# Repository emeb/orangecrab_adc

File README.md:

# orangecrab_adc
An ADC and audio FeatherWing to enable SDR experiments with the OrangeCrab

## What is it?
This is an experiment to see if a low-spec SDR system can be easily built
using the OrangeCrab FPGA Feather. It will consist of the ADC / Audio 
"FeatherWing" board which attaches to the OrangeCrab board, along with
gateware to do basic tuning and demodulation. Initial testing will be
static setups, or controlled by USB, but the project may be expanded with
a UI board containing display and buttons / encoders.

## Features
The board comprises the following components:

* AD9203 10-bit / 40MSPS parallel ADC
* 40MHz crystal oscillator
* Analog supply regulation
* 50-ohm SMA input with transformer-coupling to the converter
* TPA6139 Headphone amplifier and 3.5mm jack
* 4-pin I2C bus extension (power, clock, data, gnd)

## Schematic

## Status
* 2020-07-24: The preliminary board design is complete and boards have been
ordered from OSHPark. Parts have been ordered so initial testing should occurr
sometime in early August 2020.

* 2020-08-08: Boards are back from OSHpark and the preliminary test gateware
is working for simple AM broadcast reception. Audio output sounds great -
very clean and clear. 

* 2020-08-09: Corrected missing mount holes in PCB. Updated OSHpark link

https://oshpark.com/shared_projects/GzvQCkin

* 2020-08-18: Added Litex-based controller project

https://github.com/emeb/OrangeCrab-Litex-ADC

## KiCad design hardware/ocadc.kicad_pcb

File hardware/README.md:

# orangecrab_adc - hardware
Hardware design for the orangecrab_adc

This is just the KiCad design. The libraries are probably hosed (as usual)
because your setup isn't the same as mine. Hopefully the rescue libs and
cache have enough that you can see things.

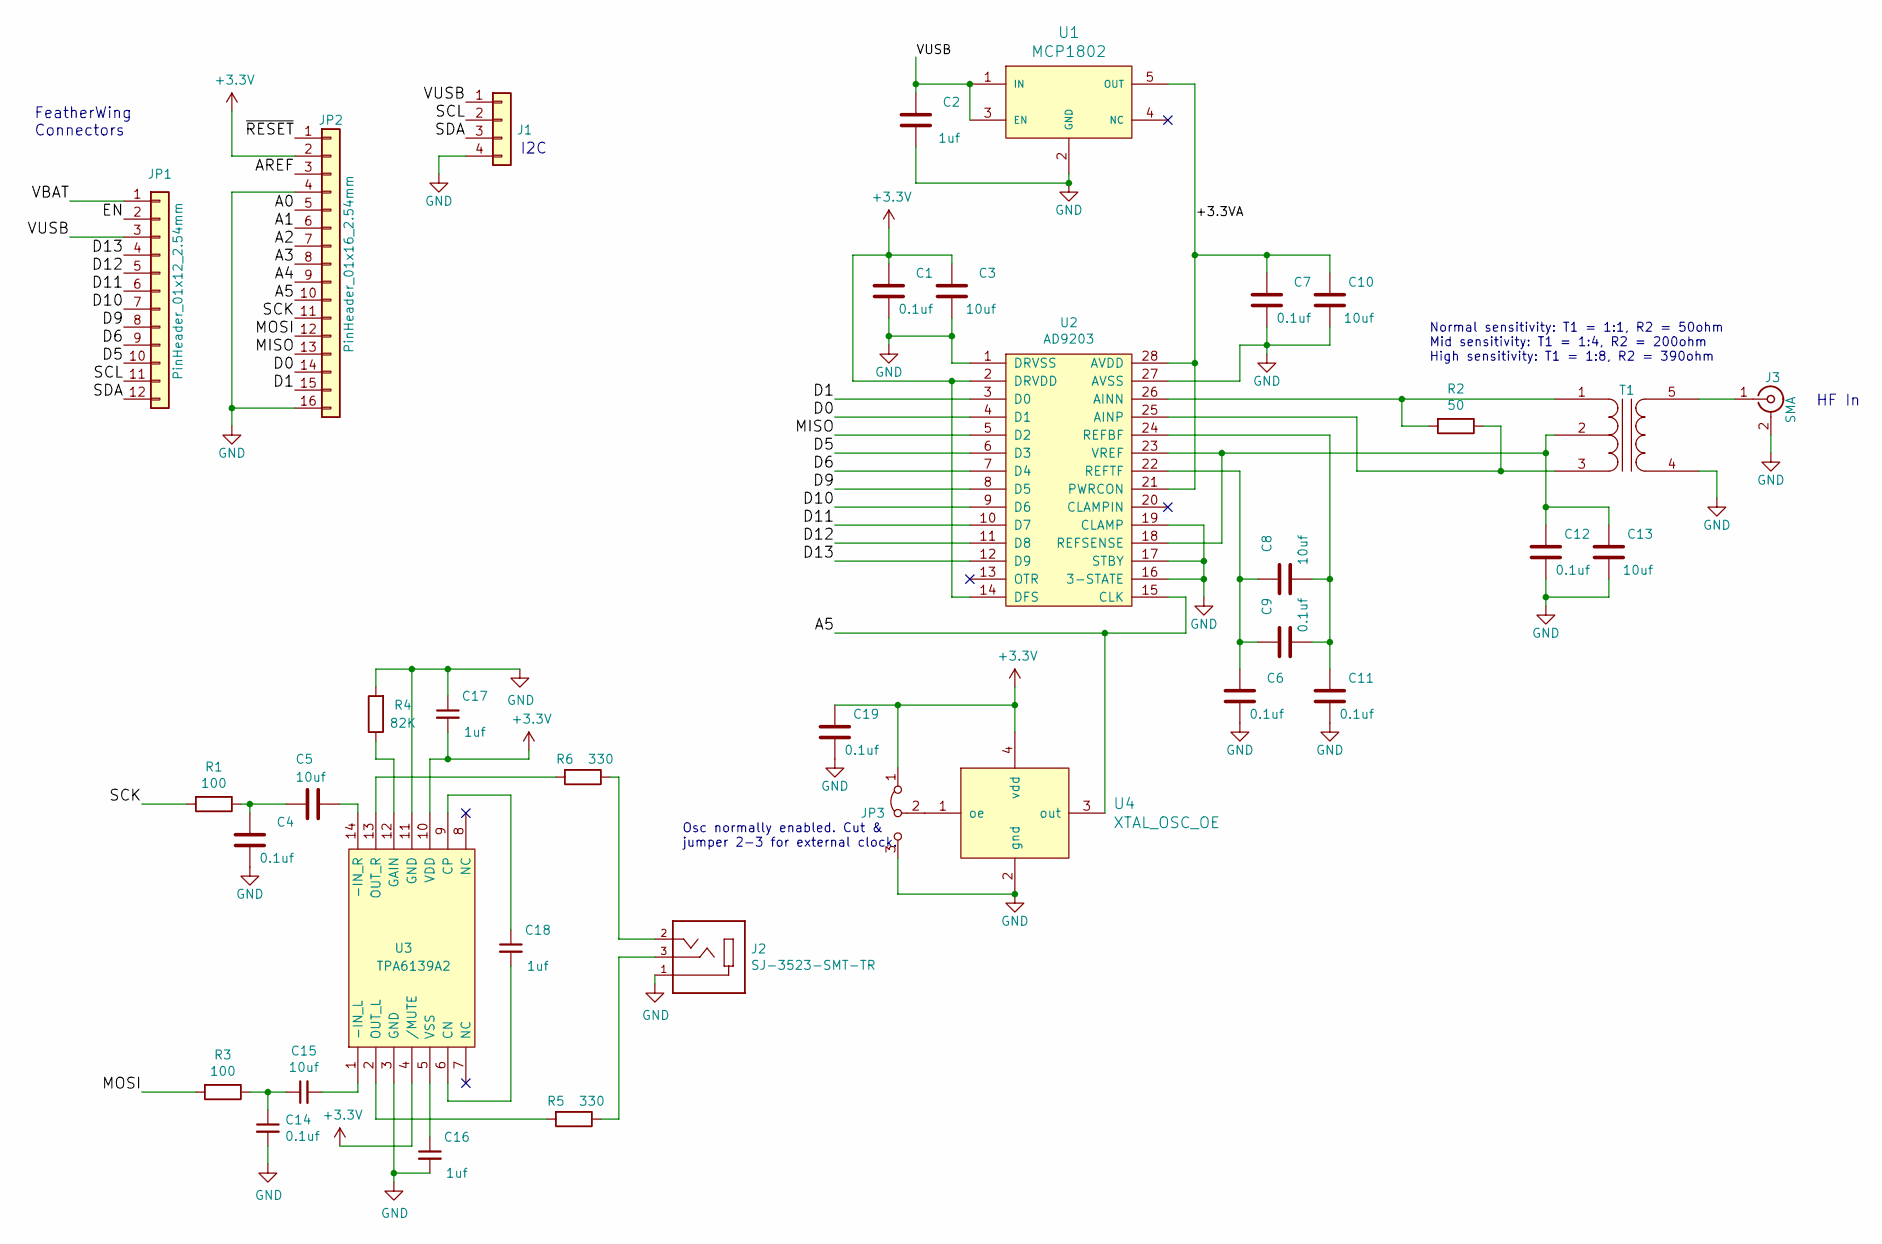
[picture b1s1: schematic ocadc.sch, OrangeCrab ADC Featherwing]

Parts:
C1, C4, C6, C7, C9, C11, C12, C14, C19: 0.1uf; C_0603_HandSoldering
C2, C16, C17, C18: 1uf; C_0603_HandSoldering
C3, C5, C8, C10, C13, C15: 10uf; C_0805_HandSoldering
J1: Conn_01x04; Pin_Header_Straight_1x04_Pitch2.54mm
J2: SJ-3523-SMT-TR; CUI_SJ-3523-SMT-TR
J3: SMA; SMA_END
JP1: PinHeader_01x12_2.54mm; Conn_PinHeader_1x12
JP2: PinHeader_01x16_2.54mm; Conn_PinHeader_1x16
JP3: Jumper_3_Bridged12; SolderJumper-3_P1.3mm_Bridged12_Pad1.0x1.5mm
R1, R3: 100; R_0603_HandSoldering
R2: 50; R_0603_HandSoldering
R4: 82K; R_0603_HandSoldering
R5, R6: 330; R_0603_HandSoldering
T1: TRANSFO4; Pulse_SMD_Balun
U1: MCP1802; SOT-23-5_HandSoldering
U2: AD9203; TSSOP-28_4.4x9.7mm_Pitch0.65mm
U3: TPA6139A2; TSSOP-14_4.4x5mm_Pitch0.65mm
U4: XTAL_OSC_OE; Oscillator_SMD_SeikoEpson_SG210-4pin_2.5x2.0mm_HandSoldering

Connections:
+3V3: C1.2, C3.2, C17.2, C19.2, JP2.2, JP3.1 (A), U2.2 (DRVDD), U2.14 (DFS), U3.4 (/MUTE), U3.10 (VDD), U4.4 (vdd)
/+3.3VA: C7.2, C10.2, U1.5 (OUT), U2.21 (PWRCON), U2.28 (AVDD)
/A0: JP2.5
/A1: JP2.6
/A2: JP2.7
/A3: JP2.8
/A4: JP2.9
/A5: JP2.10, U2.15 (CLK), U4.3 (out)
/AREF: JP2.3
/D0: JP2.14, U2.4 (D1)
/D1: JP2.15, U2.3 (D0)
/D5: JP1.10, U2.6 (D3)
/D6: JP1.9, U2.7 (D4)
/D9: JP1.8, U2.8 (D5)
/D10: JP1.7, U2.9 (D6)
/D11: JP1.6, U2.10 (D7)
/D12: JP1.5, U2.11 (D8)
/D13: JP1.4, U2.12 (D9)
/EN: JP1.2
/MISO: JP2.13, U2.5 (D2)
/MOSI: JP2.12, R3.2
/SCK: JP2.11, R1.2
/SCL: J1.2, JP1.11
/SDA: J1.3, JP1.12
/VBAT: JP1.1
/VUSB: C2.2, J1.1, JP1.3, U1.1 (IN), U1.3 (EN)
/~RESET: JP2.1
GND: C1.1, C2.1, C3.1, C4.1, C6.1, C7.1, C10.1, C11.1, C12.1, C13.1, C14.2, C16.2, C17.1, C19.1, J1.4, J2.1, J3.2 (Ext), JP2.4, JP2.16, JP3.3 (B), R4.2, T1.4 (S1), U1.2 (GND), U2.1 (DRVSS), U2.16 (3-STATE), U2.17 (STBY), U2.19 (CLAMP), U2.27 (AVSS), U3.3 (GND), U3.11 (GND), U4.2 (gnd)
unnamed: C4.2, C5.2, R1.1
unnamed: C5.1, U3.14 (-IN_R)
unnamed: C6.2, C8.2, C9.2, U2.22 (REFTF)
unnamed: C8.1, C9.1, C11.2, U2.24 (REFBF)
unnamed: C12.2, C13.2, T1.2 (PM), U2.18 (REFSENSE), U2.23 (VREF)
unnamed: C14.1, C15.1, R3.1
unnamed: C15.2, U3.1 (-IN_L)
unnamed: C16.1, U3.5 (VSS)
unnamed: C18.1, U3.9 (CP)
unnamed: C18.2, U3.6 (CN)
unnamed: J2.2, R6.1
unnamed: J2.3, R5.1
unnamed: J3.1 (In), T1.5 (S2)
unnamed: JP3.2 (C), U4.1 (oe)
unnamed: R2.1, T1.3 (PR2), U2.25 (AINP)
unnamed: R2.2, T1.1 (PR1), U2.26 (AINN)
unnamed: R4.1, U3.12 (GAIN)
unnamed: R5.2, U3.2 (OUT_L)
unnamed: R6.2, U3.13 (OUT_R)

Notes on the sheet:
HF In
FeatherWing Connectors
I2C
Normal sensitivity: T1 = 1:1, R2 = 50ohm Mid sensitivity: T1 = 1:4, R2 = 200ohm High sensitivity: T1 = 1:8, R2 = 390ohm
Osc normally enabled. Cut & jumper 2-3 for external clock.

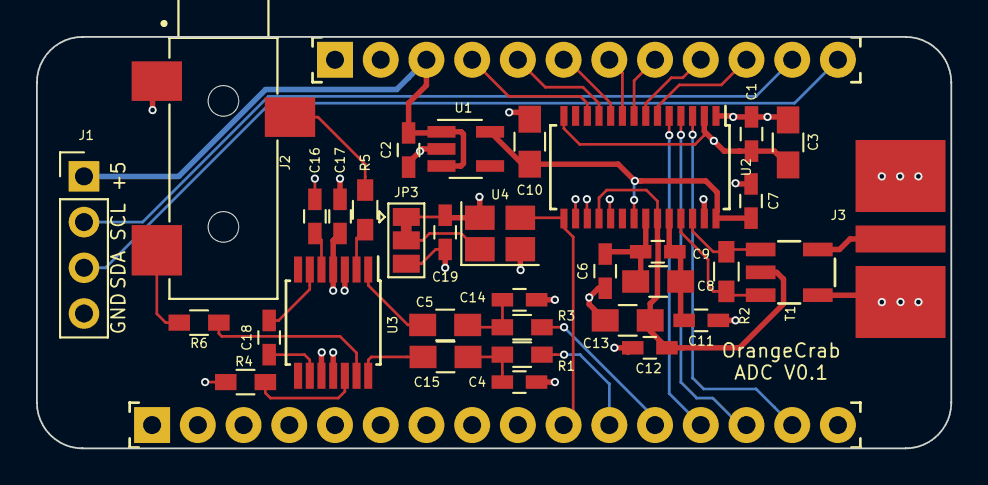
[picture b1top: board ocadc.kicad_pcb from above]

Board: 4 copper layers, 50.8 x 22.9 mm, 36 parts (0 on the bottom side), 38 nets.

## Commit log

2020-07-23 Initial checkin of ocadc materials
2020-08-01 Added verilgo and nmigen preliminary designs
2020-08-01 Added nmigen README.
2020-08-02 Clean up / simplify platform extensions
2020-08-05 Added demodulators
2020-08-08 Updated with working board
2020-08-08 Fix image type
2020-08-09 new layout
2020-08-18 Updated with new Litex project

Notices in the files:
hardware/ocadc.kicad_pcb:
(c) 2020 E. Brombaugh
